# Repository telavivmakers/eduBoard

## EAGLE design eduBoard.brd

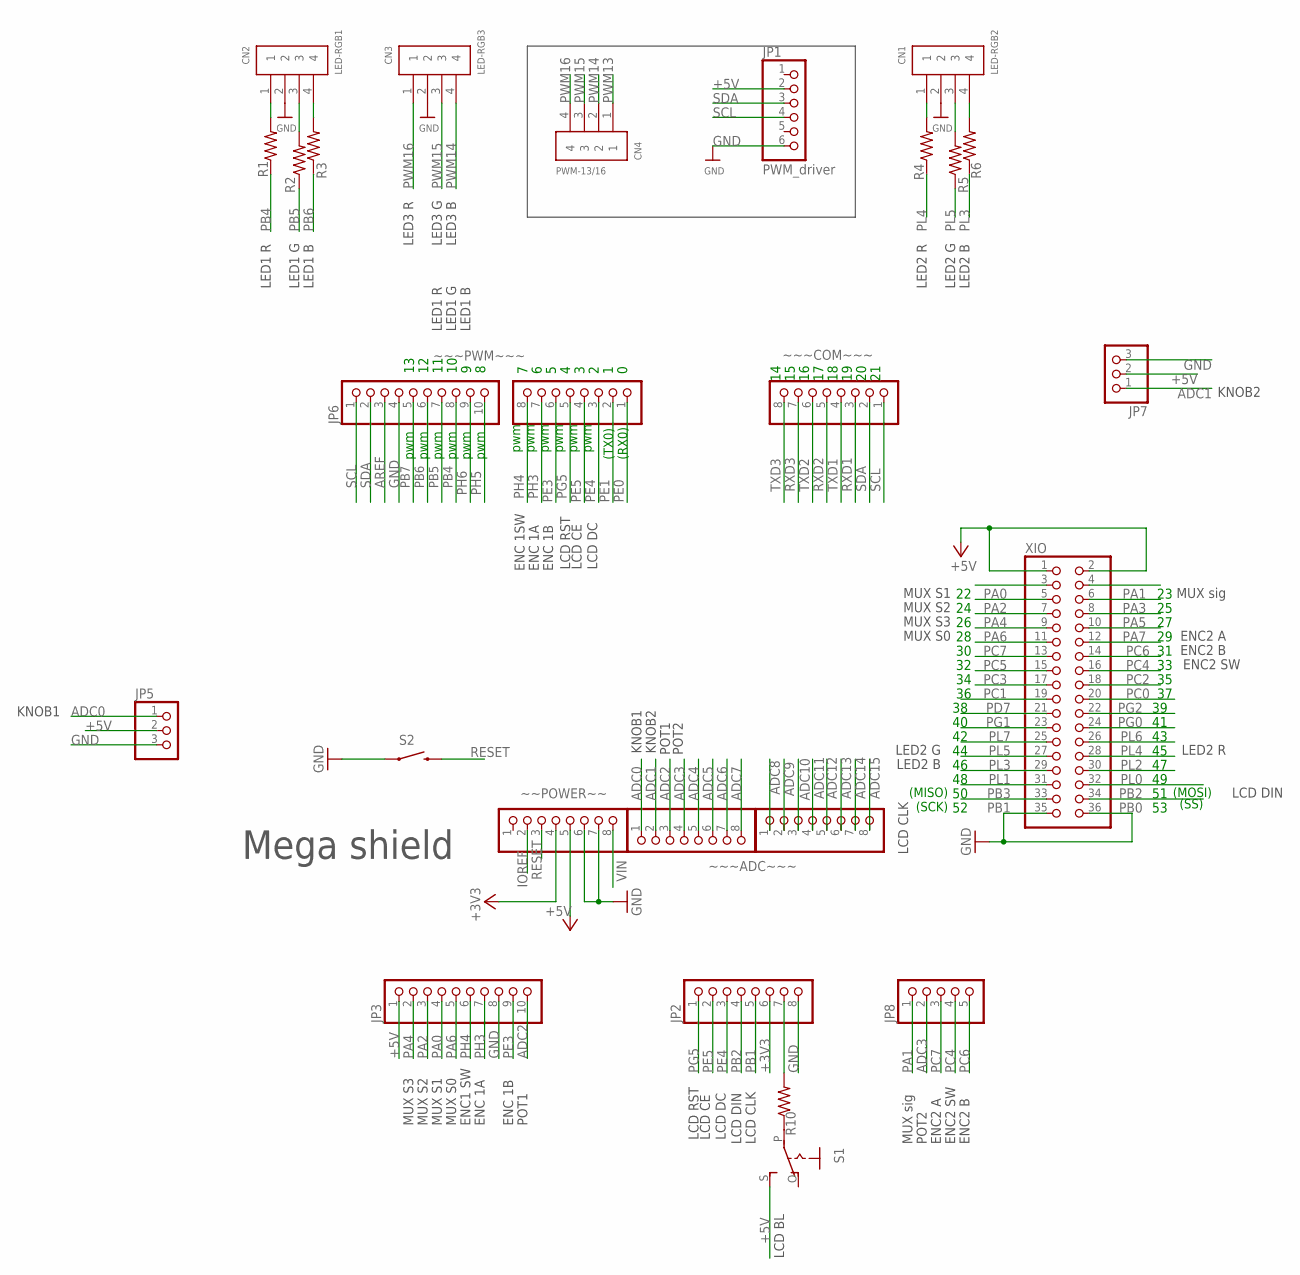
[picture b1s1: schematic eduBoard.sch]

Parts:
ADCL: 8x1F-H8.5; 1X08
CN1: LED-RGB2; 1X04-BIG
CN2: LED-RGB1; 1X04-BIG
CN3: LED-RGB3; 1X04-BIG
CN4: PWM-13/16; 1X04-BIG
JP1: PWM_driver; 1X06
JP2: PINHD-1X8OVAL; 1X08-OVAL
JP3: PINHD-1X10_ARD; 1X10
JP5, JP7: PINHD-1X3; 1X03
JP6: 10x1F-H8.5; 1X10
JP8: HEADER-1X5; 1X05_OVAL
R1, R2, R3, R4, R5, R6, R10: R-US_0207/10; 0207/10
S1: EG1218S; EG1218
S2: SWITCH-MOMENTARY-2PTH; TACTILE-PTH
XIO: 18x2F-H8.5; 2X18
~~POWER~~: 8x1F-H8.5; 1X08
~~~ADC~~~: 8x1F-H8.5; 1X08
~~~COM~~~: 8x1F-H8.5; 1X08
~~~PWM~~~: 8x1F-H8.5; 1X08

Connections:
+3V3: JP2.6, ~~POWER~~.4
+5V: JP1.2, JP3.1, JP5.2, JP7.2, S1.S, XIO.1, XIO.2, ~~POWER~~.5
ADC0: ADCL.1, JP5.1
ADC1: ADCL.2, JP7.1
ADC2: ADCL.3, JP3.10
ADC3: ADCL.4, JP8.2
ADC4: ADCL.5
ADC5: ADCL.6
ADC6: ADCL.7
ADC7: ADCL.8
ADC8: ~~~ADC~~~.1
ADC9: ~~~ADC~~~.2
ADC10: ~~~ADC~~~.3
ADC11: ~~~ADC~~~.4
ADC12: ~~~ADC~~~.5
ADC13: ~~~ADC~~~.6
ADC14: ~~~ADC~~~.7
ADC15: ~~~ADC~~~.8
AREF: JP6.3
GND: CN1.2, CN2.2, CN3.2, JP1.6, JP2.8, JP3.8, JP5.3, JP6.4, JP7.3, S2.1, XIO.35, XIO.36, ~~POWER~~.6, ~~POWER~~.7
IOREF: ~~POWER~~.2
unnamed: CN2.3, R2.2
unnamed: CN2.4, R3.2
unnamed: CN1.1, R4.2
unnamed: CN1.4, R6.2
unnamed: CN2.1, R1.2
unnamed: JP2.7, R10.2
unnamed: CN1.3, R5.2
unnamed: R10.1, S1.P
PA0: JP3.4, XIO.3
PA1: JP8.1, XIO.4
PA2: JP3.3, XIO.5
PA3: XIO.6
PA4: JP3.2, XIO.7
PA5: XIO.8
PA6: JP3.5, XIO.9
PA7: XIO.10
PB0: XIO.34
PB1: JP2.5, XIO.33
PB2: JP2.4, XIO.32
PB3: XIO.31
PB4: JP6.8, R1.1
PB5: JP6.7, R2.1
PB6: JP6.6, R3.1
PB7: JP6.5
PC0: XIO.18
PC1: XIO.17
PC2: XIO.16
PC3: XIO.15
PC4: JP8.4, XIO.14
PC5: XIO.13
PC6: JP8.5, XIO.12
PC7: JP8.3, XIO.11
PD7: XIO.19
PE0: ~~~PWM~~~.1
PE1: ~~~PWM~~~.2
PE3: JP3.9, ~~~PWM~~~.6
PE4: JP2.3, ~~~PWM~~~.3
PE5: JP2.2, ~~~PWM~~~.4
PG0: XIO.22
PG1: XIO.21
PG2: XIO.20
PG5: JP2.1, ~~~PWM~~~.5
PH3: JP3.7, ~~~PWM~~~.7
PH4: JP3.6, ~~~PWM~~~.8
PH5: JP6.10
PH6: JP6.9
PL0: XIO.30
PL1: XIO.29
PL2: XIO.28
PL3: R6.1, XIO.27
PL4: R4.1, XIO.26
PL5: R5.1, XIO.25
PL6: XIO.24
PL7: XIO.23
PWM13: CN4.1
PWM14: CN3.4, CN4.2
PWM15: CN3.3, CN4.3
PWM16: CN3.1, CN4.4
RESET: S2.3 (2), ~~POWER~~.3
RXD1: ~~~COM~~~.3
RXD2: ~~~COM~~~.5
RXD3: ~~~COM~~~.7
SCL: JP1.4, JP6.1, ~~~COM~~~.1
SDA: JP1.3, JP6.2, ~~~COM~~~.2
TXD1: ~~~COM~~~.4
TXD2: ~~~COM~~~.6
TXD3: ~~~COM~~~.8
VIN: ~~POWER~~.8

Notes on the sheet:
pwm
(TX0)
(RX0)
(SS)
(MOSI)
(SCK)
(MISO)
Mega shield
LCD CE
LCD DC
LCD RST
ENC 1B
ENC 1SW
ENC 1A
LCD DIN
LCD CLK
LCD BL
ENC2 A
ENC2 B
ENC2 SW
POT2
MUX sig
MUX S3
MUX S2
MUX S1
MUX S0
ENC1 SW
POT1
KNOB1
KNOB2
LED3 R
LED3 G
LED3 B
LED2 R
LED2 G
LED2 B
LED1 R
LED1 G
LED1 B

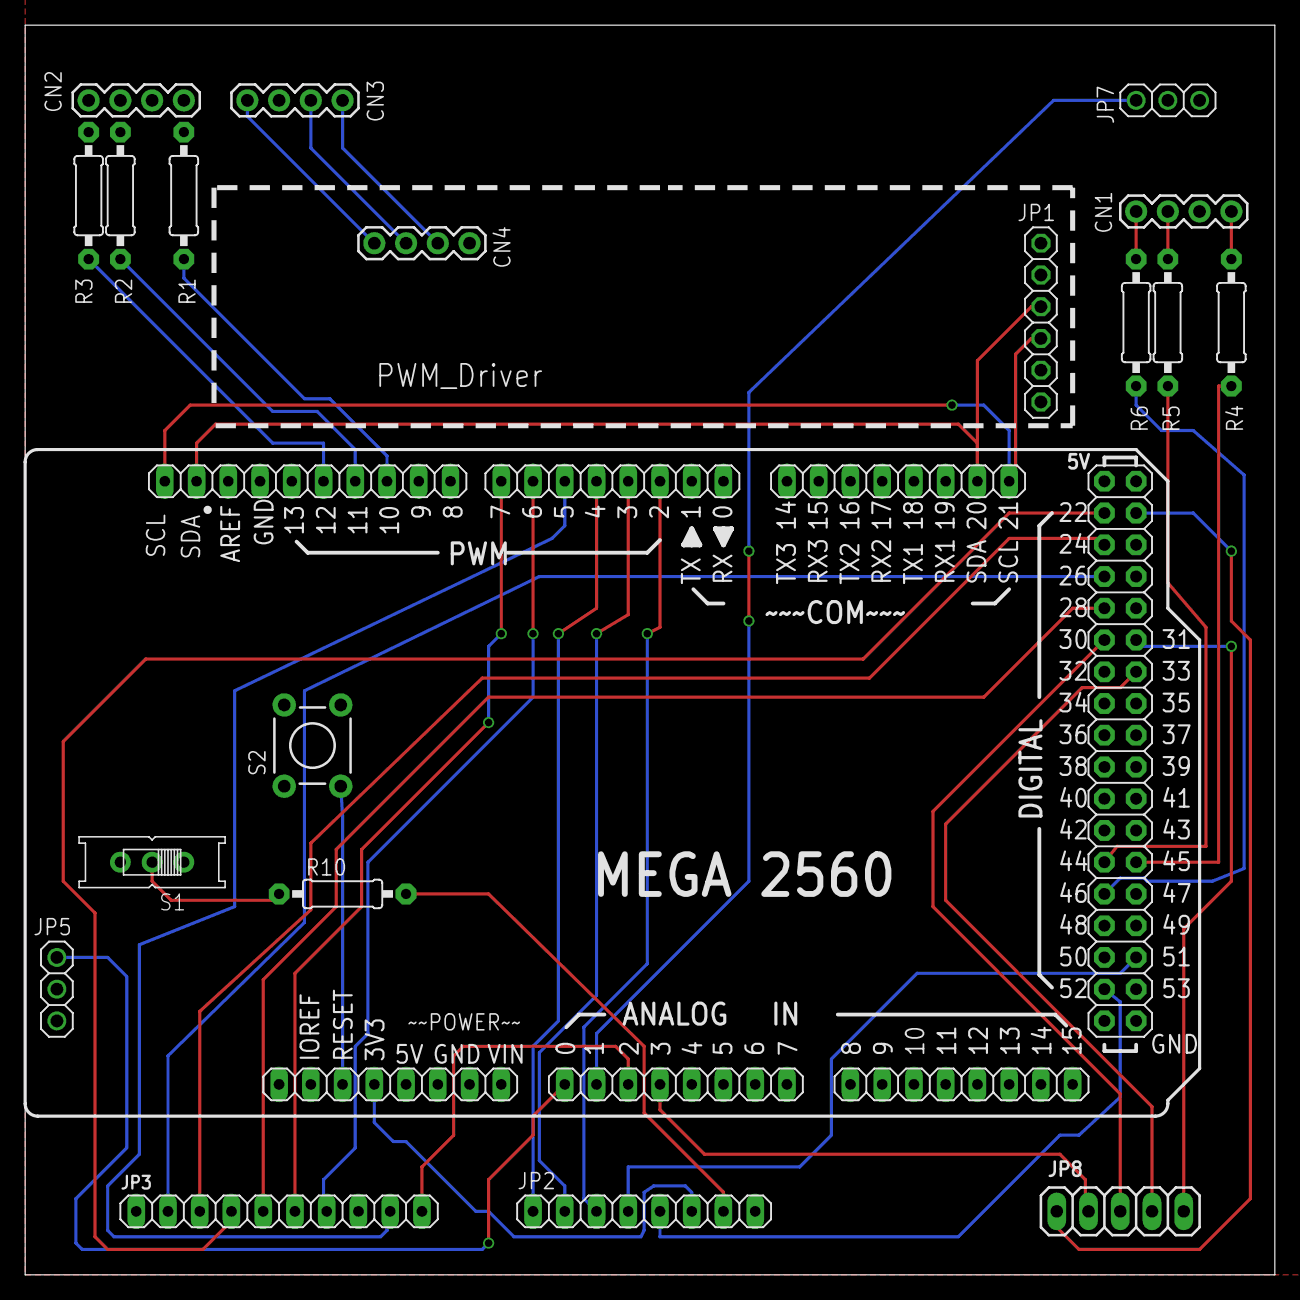
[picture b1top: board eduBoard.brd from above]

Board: 2 copper layers, 100.0 x 100.0 mm, 26 parts (0 on the bottom side), 43 nets.

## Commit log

2016-10-17 added ronen draft and Arduino_MEGA_2560-Rev3
2016-10-17 nicer mega shield
2016-10-18 schema work, not final
2016-10-18 add pic of proto board
2016-10-22 updates, ready for beutification
2016-10-22 ready to work on SVG silkscreen
2016-10-22 update layout
2016-10-22 added pin assignment doc into board silk screen
2016-10-22 typo in silk screen
2016-10-22 pushed
2016-10-22 minor svg changes, bit bigger fonts
2016-10-22 minor svg changes, bit bigger fonts, 5x5font
2016-10-23 all fonts as paths
2016-10-25 moved slikscreen to correct place -100mil, -200mil (xy) using grebv!
2016-10-25 routed missing i2c
2016-10-26 routed
2016-10-27 adedded silkscren>SVG>gerber workflow readme

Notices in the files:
parts and their libraries:
microbuilder: This work is placed in the public domain, and may be freely used for commercial and non-commercial work with the following conditions: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
